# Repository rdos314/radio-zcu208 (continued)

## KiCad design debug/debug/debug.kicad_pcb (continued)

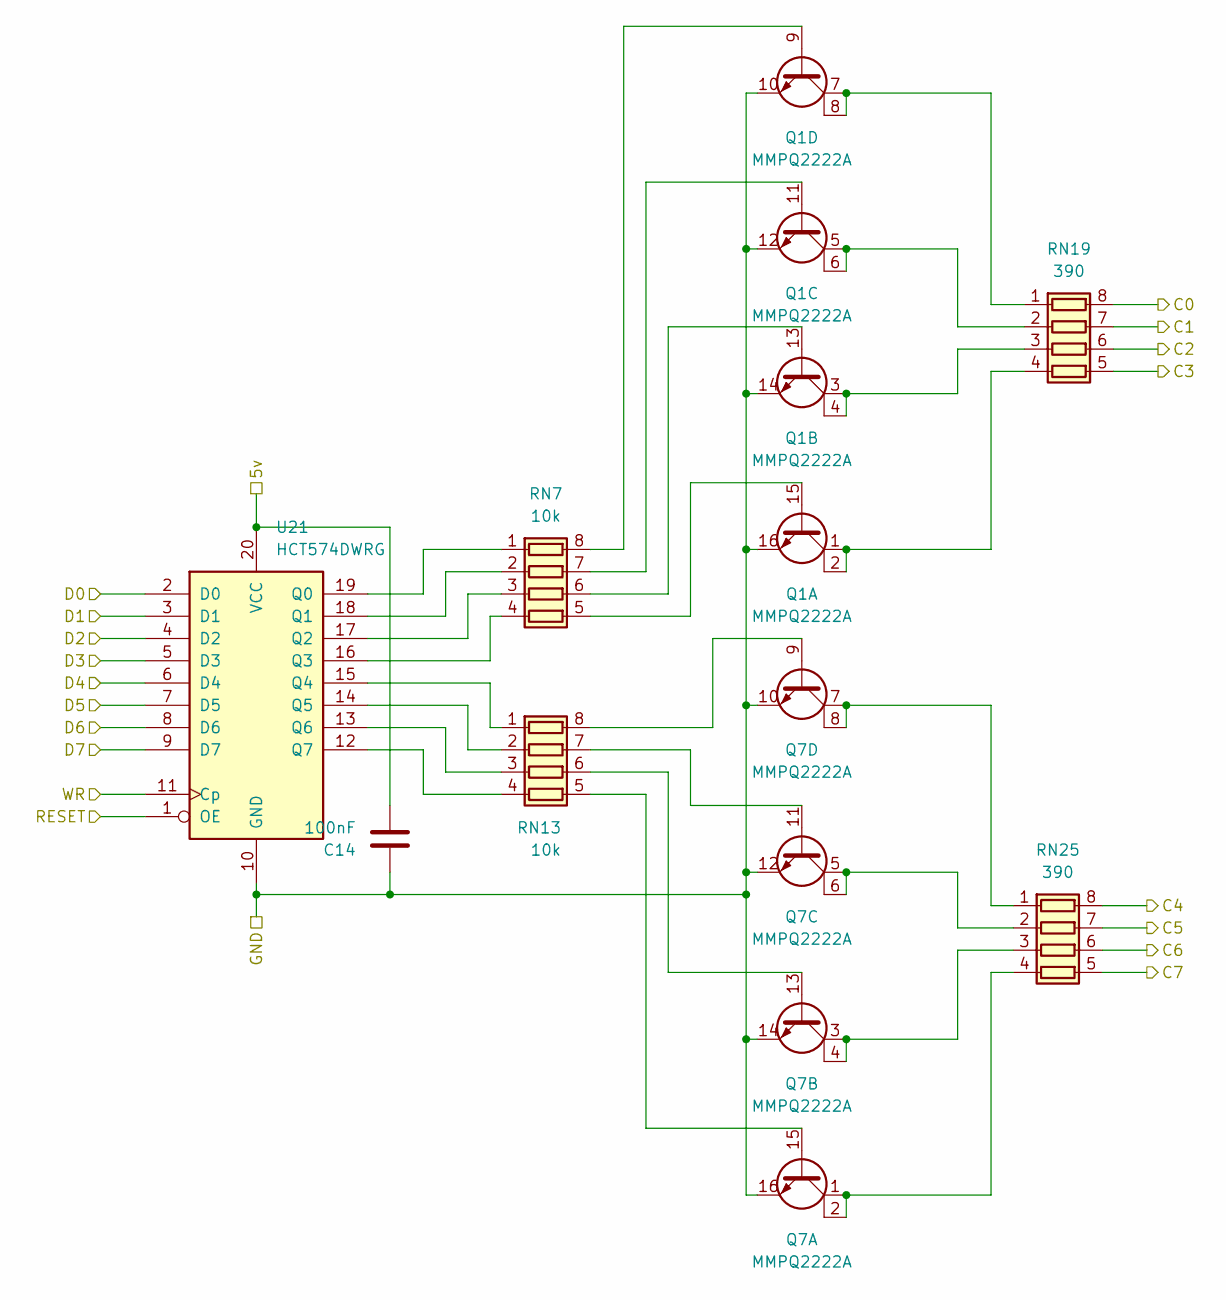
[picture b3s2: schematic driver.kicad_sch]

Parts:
C14: 100nF; C_0805_2012Metric_Pad1.18x1.45mm_HandSolder
Q1, Q7: MMPQ2222A; SO-16_3.9x9.9mm_P1.27mm
RN7, RN13: 10k; R_Array_Convex_4x0603
RN19, RN25: 390; R_Array_Convex_4x0603
U21: HCT574DWRG; SOIC-20W_7.5x12.8mm_P1.27mm

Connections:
5v: C14.2, U21.20 (VCC); also elsewhere on the board
/Band_Low/driver-LSB/C0: RN19.8 (R1.2); also elsewhere on the board
/Band_Low/driver-LSB/C1: RN19.7 (R2.2); also elsewhere on the board
/Band_Low/driver-LSB/C2: RN19.6 (R3.2); also elsewhere on the board
/Band_Low/driver-LSB/C3: RN19.5 (R4.2); also elsewhere on the board
/Band_Low/driver-LSB/C4: RN25.8 (R1.2); also elsewhere on the board
/Band_Low/driver-LSB/C5: RN25.7 (R2.2); also elsewhere on the board
/Band_Low/driver-LSB/C6: RN25.6 (R3.2); also elsewhere on the board
/Band_Low/driver-LSB/C7: RN25.5 (R4.2); also elsewhere on the board
D0: U21.2 (D0); also elsewhere on the board
D1: U21.3 (D1); also elsewhere on the board
D2: U21.4 (D2); also elsewhere on the board
D3: U21.5 (D3); also elsewhere on the board
D4: U21.6 (D4); also elsewhere on the board
D5: U21.7 (D5); also elsewhere on the board
D6: U21.8 (D6); also elsewhere on the board
D7: U21.9 (D7); also elsewhere on the board
GND: C14.1, Q1.10 (E), Q1.12 (E), Q1.14 (E), Q1.16 (E), Q7.10 (E), Q7.12 (E), Q7.14 (E), Q7.16 (E), U21.10 (GND); also elsewhere on the board
LED_LSB_LOW_WR: U21.11 (Cp); also elsewhere on the board
LED_RESET: U21.1 (OE); also elsewhere on the board
unnamed: Q1.15 (B), RN7.5 (R4.2)
unnamed: Q1.13 (B), RN7.6 (R3.2)
unnamed: Q1.11 (B), RN7.7 (R2.2)
unnamed: Q1.9 (B), RN7.8 (R1.2)
unnamed: Q7.15 (B), RN13.5 (R4.2)
unnamed: Q7.13 (B), RN13.6 (R3.2)
unnamed: Q7.11 (B), RN13.7 (R2.2)
unnamed: Q7.9 (B), RN13.8 (R1.2)
unnamed: RN7.1 (R1.1), U21.19 (Q0)
unnamed: RN7.2 (R2.1), U21.18 (Q1)
unnamed: RN7.3 (R3.1), U21.17 (Q2)
unnamed: RN7.4 (R4.1), U21.16 (Q3)
unnamed: RN13.1 (R1.1), U21.15 (Q4)
unnamed: RN13.2 (R2.1), U21.14 (Q5)
unnamed: RN13.3 (R3.1), U21.13 (Q6)
unnamed: RN13.4 (R4.1), U21.12 (Q7)
unnamed: Q1.7 (C), Q1.8 (C), RN19.1 (R1.1)
unnamed: Q1.5 (C), Q1.6 (C), RN19.2 (R2.1)
unnamed: Q1.3 (C), Q1.4 (C), RN19.3 (R3.1)
unnamed: Q1.1 (C), Q1.2 (C), RN19.4 (R4.1)
unnamed: Q7.7 (C), Q7.8 (C), RN25.1 (R1.1)
unnamed: Q7.5 (C), Q7.6 (C), RN25.2 (R2.1)
unnamed: Q7.3 (C), Q7.4 (C), RN25.3 (R3.1)
unnamed: Q7.1 (C), Q7.2 (C), RN25.4 (R4.1)

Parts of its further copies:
C16, C17, C18, C19, C20, C21: 100nF; C_0805_2012Metric_Pad1.18x1.45mm_HandSolder
Q2, Q3, Q4, Q5, Q6, Q8, Q9, Q10, Q11, Q12, Q13, Q14: MMPQ2222A; SO-16_3.9x9.9mm_P1.27mm
RN8, RN9, RN10, RN11, RN12, RN14, RN15, RN16, RN17, RN18, RN31, RN32: 10k; R_Array_Convex_4x0603
RN20, RN21, RN22, RN23, RN24, RN26, RN27, RN28, RN29, RN30, RN33, RN34: 390; R_Array_Convex_4x0603
U22, U23, U24, U25, U26, U27: HCT574DWRG; SOIC-20W_7.5x12.8mm_P1.27mm

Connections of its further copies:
5v: C16.2, C17.2, C18.2, C19.2, C20.2, C21.2, U22.20 (VCC), U23.20 (VCC), U24.20 (VCC), U25.20 (VCC), U26.20 (VCC), U27.20 (VCC); also elsewhere on the board
/Band_High/driver-LSB/C0: RN20.8 (R1.2); also elsewhere on the board
/Band_High/driver-LSB/C1: RN20.7 (R2.2); also elsewhere on the board
/Band_High/driver-LSB/C2: RN20.6 (R3.2); also elsewhere on the board
/Band_High/driver-LSB/C3: RN20.5 (R4.2); also elsewhere on the board
/Band_High/driver-LSB/C4: RN26.8 (R1.2); also elsewhere on the board
/Band_High/driver-LSB/C5: RN26.7 (R2.2); also elsewhere on the board
/Band_High/driver-LSB/C6: RN26.6 (R3.2); also elsewhere on the board
/Band_High/driver-LSB/C7: RN26.5 (R4.2); also elsewhere on the board
/Band_High/driver-MSB/C0: RN22.8 (R1.2); also elsewhere on the board
/Band_High/driver-MSB/C1: RN22.7 (R2.2); also elsewhere on the board
/Band_High/driver-MSB/C2: RN22.6 (R3.2); also elsewhere on the board
/Band_High/driver-MSB/C3: RN22.5 (R4.2); also elsewhere on the board
/Band_High/driver-MSB/C4: RN28.8 (R1.2); also elsewhere on the board
/Band_High/driver-MSB/C5: RN28.7 (R2.2); also elsewhere on the board
/Band_High/driver-MSB/C6: RN28.6 (R3.2); also elsewhere on the board
/Band_High/driver-MSB/C7: RN28.5 (R4.2); also elsewhere on the board
/Band_High/driver-dir/C0: RN24.8 (R1.2); also elsewhere on the board
/Band_High/driver-dir/C1: RN24.7 (R2.2); also elsewhere on the board
/Band_High/driver-dir/C2: RN24.6 (R3.2); also elsewhere on the board
/Band_High/driver-dir/C3: RN24.5 (R4.2); also elsewhere on the board
/Band_High/driver-dir/C4: RN30.8 (R1.2); also elsewhere on the board
/Band_High/driver-dir/C5: RN30.7 (R2.2); also elsewhere on the board
/Band_High/driver-dir/C6: RN30.6 (R3.2); also elsewhere on the board
/Band_High/driver-dir/C7: RN30.5 (R4.2); also elsewhere on the board
/Band_Low/driver-MSB/C0: RN21.8 (R1.2); also elsewhere on the board
/Band_Low/driver-MSB/C1: RN21.7 (R2.2); also elsewhere on the board
/Band_Low/driver-MSB/C2: RN21.6 (R3.2); also elsewhere on the board
/Band_Low/driver-MSB/C3: RN21.5 (R4.2); also elsewhere on the board
/Band_Low/driver-MSB/C4: RN27.8 (R1.2); also elsewhere on the board
/Band_Low/driver-MSB/C5: RN27.7 (R2.2); also elsewhere on the board
/Band_Low/driver-MSB/C6: RN27.6 (R3.2); also elsewhere on the board
/Band_Low/driver-MSB/C7: RN27.5 (R4.2); also elsewhere on the board
/Band_Low/driver-dir/C0: RN23.8 (R1.2); also elsewhere on the board
/Band_Low/driver-dir/C1: RN23.7 (R2.2); also elsewhere on the board
/Band_Low/driver-dir/C2: RN23.6 (R3.2); also elsewhere on the board
/Band_Low/driver-dir/C3: RN23.5 (R4.2); also elsewhere on the board
/Band_Low/driver-dir/C4: RN29.8 (R1.2); also elsewhere on the board
/Band_Low/driver-dir/C5: RN29.7 (R2.2); also elsewhere on the board
/Band_Low/driver-dir/C6: RN29.6 (R3.2); also elsewhere on the board
/Band_Low/driver-dir/C7: RN29.5 (R4.2); also elsewhere on the board
/driver-status/C0: RN34.8 (R1.2); also elsewhere on the board
/driver-status/C1: RN34.7 (R2.2); also elsewhere on the board
/driver-status/C2: RN34.6 (R3.2); also elsewhere on the board
/driver-status/C3: RN34.5 (R4.2); also elsewhere on the board
/driver-status/C4: RN33.8 (R1.2); also elsewhere on the board
/driver-status/C5: RN33.7 (R2.2); also elsewhere on the board
D0: U22.2 (D0), U23.2 (D0), U24.2 (D0), U25.2 (D0), U26.2 (D0), U27.2 (D0); also elsewhere on the board
D1: U22.3 (D1), U23.3 (D1), U24.3 (D1), U25.3 (D1), U26.3 (D1), U27.3 (D1); also elsewhere on the board
D2: U22.4 (D2), U23.4 (D2), U24.4 (D2), U25.4 (D2), U26.4 (D2), U27.4 (D2); also elsewhere on the board
D3: U22.5 (D3), U23.5 (D3), U24.5 (D3), U25.5 (D3), U26.5 (D3), U27.5 (D3); also elsewhere on the board
D4: U22.6 (D4), U23.6 (D4), U24.6 (D4), U25.6 (D4), U26.6 (D4), U27.6 (D4); also elsewhere on the board
D5: U22.7 (D5), U23.7 (D5), U24.7 (D5), U25.7 (D5), U26.7 (D5), U27.7 (D5); also elsewhere on the board
D6: U22.8 (D6), U23.8 (D6), U24.8 (D6), U25.8 (D6), U26.8 (D6), U27.8 (D6); also elsewhere on the board
D7: U22.9 (D7), U23.9 (D7), U24.9 (D7), U25.9 (D7), U26.9 (D7), U27.9 (D7); also elsewhere on the board
DIR_HIGH_ERR: RN33.5 (R4.2); also elsewhere on the board
DIR_HIGH_WR: U26.11 (Cp); also elsewhere on the board
DIR_LOW_ERR: RN33.6 (R3.2); also elsewhere on the board
DIR_LOW_WR: U25.11 (Cp); also elsewhere on the board
GND: C16.1, C17.1, C18.1, C19.1, C20.1, C21.1, Q2.10 (E), Q2.12 (E), Q2.14 (E), Q2.16 (E), Q3.10 (E), Q3.12 (E), Q3.14 (E), Q3.16 (E), Q4.10 (E), Q4.12 (E), Q4.14 (E), Q4.16 (E), Q5.10 (E), Q5.12 (E), Q5.14 (E), Q5.16 (E), Q6.10 (E), Q6.12 (E), Q6.14 (E), Q6.16 (E), Q8.10 (E), Q8.12 (E), Q8.14 (E), Q8.16 (E), Q9.10 (E), Q9.12 (E), Q9.14 (E), Q9.16 (E), Q10.10 (E), Q10.12 (E), Q10.14 (E), Q10.16 (E), Q11.10 (E), Q11.12 (E), Q11.14 (E), Q11.16 (E), Q12.10 (E), Q12.12 (E), Q12.14 (E), Q12.16 (E), Q13.10 (E), Q13.12 (E), Q13.14 (E), Q13.16 (E), Q14.10 (E), Q14.12 (E), Q14.14 (E), Q14.16 (E), U22.10 (GND), U23.10 (GND), U24.10 (GND), U25.10 (GND), U26.10 (GND), U27.10 (GND); also elsewhere on the board
LED_LSB_HIGH_WR: U22.11 (Cp); also elsewhere on the board
LED_MSB_HIGH_WR: U24.11 (Cp); also elsewhere on the board
LED_MSB_LOW_WR: U23.11 (Cp); also elsewhere on the board
LED_RESET: U22.1 (OE), U23.1 (OE), U24.1 (OE), U25.1 (OE), U26.1 (OE), U27.1 (OE); also elsewhere on the board
unnamed: Q2.15 (B), RN8.5 (R4.2)
unnamed: Q2.13 (B), RN8.6 (R3.2)
unnamed: Q2.11 (B), RN8.7 (R2.2)
unnamed: Q2.9 (B), RN8.8 (R1.2)
unnamed: Q3.15 (B), RN9.5 (R4.2)
unnamed: Q3.13 (B), RN9.6 (R3.2)
unnamed: Q3.11 (B), RN9.7 (R2.2)
unnamed: Q3.9 (B), RN9.8 (R1.2)
unnamed: Q4.15 (B), RN10.5 (R4.2)
unnamed: Q4.13 (B), RN10.6 (R3.2)
unnamed: Q4.11 (B), RN10.7 (R2.2)
unnamed: Q4.9 (B), RN10.8 (R1.2)
unnamed: Q5.15 (B), RN11.5 (R4.2)
unnamed: Q5.13 (B), RN11.6 (R3.2)
unnamed: Q5.11 (B), RN11.7 (R2.2)
unnamed: Q5.9 (B), RN11.8 (R1.2)
unnamed: Q6.15 (B), RN12.5 (R4.2)
unnamed: Q6.13 (B), RN12.6 (R3.2)
unnamed: Q6.11 (B), RN12.7 (R2.2)
unnamed: Q6.9 (B), RN12.8 (R1.2)
unnamed: Q8.15 (B), RN14.5 (R4.2)
unnamed: Q8.13 (B), RN14.6 (R3.2)
unnamed: Q8.11 (B), RN14.7 (R2.2)
unnamed: Q8.9 (B), RN14.8 (R1.2)
unnamed: Q9.15 (B), RN15.5 (R4.2)
unnamed: Q9.13 (B), RN15.6 (R3.2)
unnamed: Q9.11 (B), RN15.7 (R2.2)
unnamed: Q9.9 (B), RN15.8 (R1.2)
unnamed: Q10.15 (B), RN16.5 (R4.2)
unnamed: Q10.13 (B), RN16.6 (R3.2)
unnamed: Q10.11 (B), RN16.7 (R2.2)
unnamed: Q10.9 (B), RN16.8 (R1.2)
unnamed: Q11.15 (B), RN17.5 (R4.2)
unnamed: Q11.13 (B), RN17.6 (R3.2)
unnamed: Q11.11 (B), RN17.7 (R2.2)
unnamed: Q11.9 (B), RN17.8 (R1.2)
unnamed: Q12.15 (B), RN18.5 (R4.2)
unnamed: Q12.13 (B), RN18.6 (R3.2)
unnamed: Q12.11 (B), RN18.7 (R2.2)
unnamed: Q12.9 (B), RN18.8 (R1.2)
unnamed: Q13.15 (B), RN31.5 (R4.2)
unnamed: Q13.13 (B), RN31.6 (R3.2)
unnamed: Q13.11 (B), RN31.7 (R2.2)
unnamed: Q13.9 (B), RN31.8 (R1.2)
unnamed: Q14.15 (B), RN32.5 (R4.2)
unnamed: Q14.13 (B), RN32.6 (R3.2)
unnamed: Q14.11 (B), RN32.7 (R2.2)
unnamed: Q14.9 (B), RN32.8 (R1.2)
unnamed: RN8.1 (R1.1), U22.19 (Q0)
unnamed: RN8.2 (R2.1), U22.18 (Q1)
unnamed: RN8.3 (R3.1), U22.17 (Q2)
unnamed: RN8.4 (R4.1), U22.16 (Q3)
unnamed: RN9.1 (R1.1), U23.19 (Q0)
unnamed: RN9.2 (R2.1), U23.18 (Q1)
unnamed: RN9.3 (R3.1), U23.17 (Q2)
unnamed: RN9.4 (R4.1), U23.16 (Q3)
unnamed: RN10.1 (R1.1), U24.19 (Q0)
unnamed: RN10.2 (R2.1), U24.18 (Q1)
unnamed: RN10.3 (R3.1), U24.17 (Q2)
unnamed: RN10.4 (R4.1), U24.16 (Q3)
unnamed: RN11.1 (R1.1), U25.19 (Q0)
unnamed: RN11.2 (R2.1), U25.18 (Q1)
unnamed: RN11.3 (R3.1), U25.17 (Q2)
unnamed: RN11.4 (R4.1), U25.16 (Q3)
unnamed: RN12.1 (R1.1), U26.19 (Q0)
unnamed: RN12.2 (R2.1), U26.18 (Q1)
unnamed: RN12.3 (R3.1), U26.17 (Q2)
unnamed: RN12.4 (R4.1), U26.16 (Q3)
unnamed: RN14.1 (R1.1), U22.15 (Q4)
unnamed: RN14.2 (R2.1), U22.14 (Q5)
unnamed: RN14.3 (R3.1), U22.13 (Q6)
unnamed: RN14.4 (R4.1), U22.12 (Q7)
unnamed: RN15.1 (R1.1), U23.15 (Q4)
unnamed: RN15.2 (R2.1), U23.14 (Q5)
unnamed: RN15.3 (R3.1), U23.13 (Q6)
unnamed: RN15.4 (R4.1), U23.12 (Q7)
unnamed: RN16.1 (R1.1), U24.15 (Q4)
unnamed: RN16.2 (R2.1), U24.14 (Q5)
unnamed: RN16.3 (R3.1), U24.13 (Q6)
unnamed: RN16.4 (R4.1), U24.12 (Q7)
unnamed: RN17.1 (R1.1), U25.15 (Q4)
unnamed: RN17.2 (R2.1), U25.14 (Q5)
unnamed: RN17.3 (R3.1), U25.13 (Q6)
unnamed: RN17.4 (R4.1), U25.12 (Q7)
unnamed: RN18.1 (R1.1), U26.15 (Q4)
unnamed: RN18.2 (R2.1), U26.14 (Q5)
unnamed: RN18.3 (R3.1), U26.13 (Q6)
unnamed: RN18.4 (R4.1), U26.12 (Q7)
unnamed: Q2.7 (C), Q2.8 (C), RN20.1 (R1.1)
unnamed: Q2.5 (C), Q2.6 (C), RN20.2 (R2.1)
unnamed: Q2.3 (C), Q2.4 (C), RN20.3 (R3.1)
unnamed: Q2.1 (C), Q2.2 (C), RN20.4 (R4.1)
unnamed: Q3.7 (C), Q3.8 (C), RN21.1 (R1.1)
unnamed: Q3.5 (C), Q3.6 (C), RN21.2 (R2.1)
unnamed: Q3.3 (C), Q3.4 (C), RN21.3 (R3.1)
unnamed: Q3.1 (C), Q3.2 (C), RN21.4 (R4.1)
unnamed: Q4.7 (C), Q4.8 (C), RN22.1 (R1.1)
unnamed: Q4.5 (C), Q4.6 (C), RN22.2 (R2.1)
unnamed: Q4.3 (C), Q4.4 (C), RN22.3 (R3.1)
unnamed: Q4.1 (C), Q4.2 (C), RN22.4 (R4.1)
unnamed: Q5.7 (C), Q5.8 (C), RN23.1 (R1.1)
unnamed: Q5.5 (C), Q5.6 (C), RN23.2 (R2.1)
unnamed: Q5.3 (C), Q5.4 (C), RN23.3 (R3.1)
unnamed: Q5.1 (C), Q5.2 (C), RN23.4 (R4.1)
unnamed: Q6.7 (C), Q6.8 (C), RN24.1 (R1.1)
unnamed: Q6.5 (C), Q6.6 (C), RN24.2 (R2.1)
unnamed: Q6.3 (C), Q6.4 (C), RN24.3 (R3.1)
unnamed: Q6.1 (C), Q6.2 (C), RN24.4 (R4.1)
unnamed: Q8.7 (C), Q8.8 (C), RN26.1 (R1.1)
unnamed: Q8.5 (C), Q8.6 (C), RN26.2 (R2.1)
unnamed: Q8.3 (C), Q8.4 (C), RN26.3 (R3.1)
unnamed: Q8.1 (C), Q8.2 (C), RN26.4 (R4.1)
unnamed: Q9.7 (C), Q9.8 (C), RN27.1 (R1.1)
unnamed: Q9.5 (C), Q9.6 (C), RN27.2 (R2.1)
unnamed: Q9.3 (C), Q9.4 (C), RN27.3 (R3.1)
unnamed: Q9.1 (C), Q9.2 (C), RN27.4 (R4.1)
unnamed: Q10.7 (C), Q10.8 (C), RN28.1 (R1.1)
unnamed: Q10.5 (C), Q10.6 (C), RN28.2 (R2.1)
unnamed: Q10.3 (C), Q10.4 (C), RN28.3 (R3.1)
unnamed: Q10.1 (C), Q10.2 (C), RN28.4 (R4.1)
unnamed: Q11.7 (C), Q11.8 (C), RN29.1 (R1.1)
unnamed: Q11.5 (C), Q11.6 (C), RN29.2 (R2.1)
unnamed: Q11.3 (C), Q11.4 (C), RN29.3 (R3.1)
unnamed: Q11.1 (C), Q11.2 (C), RN29.4 (R4.1)
unnamed: Q12.7 (C), Q12.8 (C), RN30.1 (R1.1)
unnamed: Q12.5 (C), Q12.6 (C), RN30.2 (R2.1)
unnamed: Q12.3 (C), Q12.4 (C), RN30.3 (R3.1)
unnamed: Q12.1 (C), Q12.2 (C), RN30.4 (R4.1)
unnamed: RN31.1 (R1.1), U27.19 (Q0)
unnamed: RN31.2 (R2.1), U27.18 (Q1)
unnamed: RN31.3 (R3.1), U27.17 (Q2)
unnamed: RN31.4 (R4.1), U27.16 (Q3)
unnamed: RN32.1 (R1.1), U27.15 (Q4)
unnamed: RN32.2 (R2.1), U27.14 (Q5)
unnamed: RN32.3 (R3.1), U27.13 (Q6)
unnamed: RN32.4 (R4.1), U27.12 (Q7)
unnamed: Q14.7 (C), Q14.8 (C), RN33.1 (R1.1)
unnamed: Q14.5 (C), Q14.6 (C), RN33.2 (R2.1)
unnamed: Q14.3 (C), Q14.4 (C), RN33.3 (R3.1)
unnamed: Q14.1 (C), Q14.2 (C), RN33.4 (R4.1)
unnamed: Q13.7 (C), Q13.8 (C), RN34.1 (R1.1)
unnamed: Q13.5 (C), Q13.6 (C), RN34.2 (R2.1)
unnamed: Q13.3 (C), Q13.4 (C), RN34.3 (R3.1)
unnamed: Q13.1 (C), Q13.2 (C), RN34.4 (R4.1)
STAT_WR: U27.11 (Cp); also elsewhere on the board

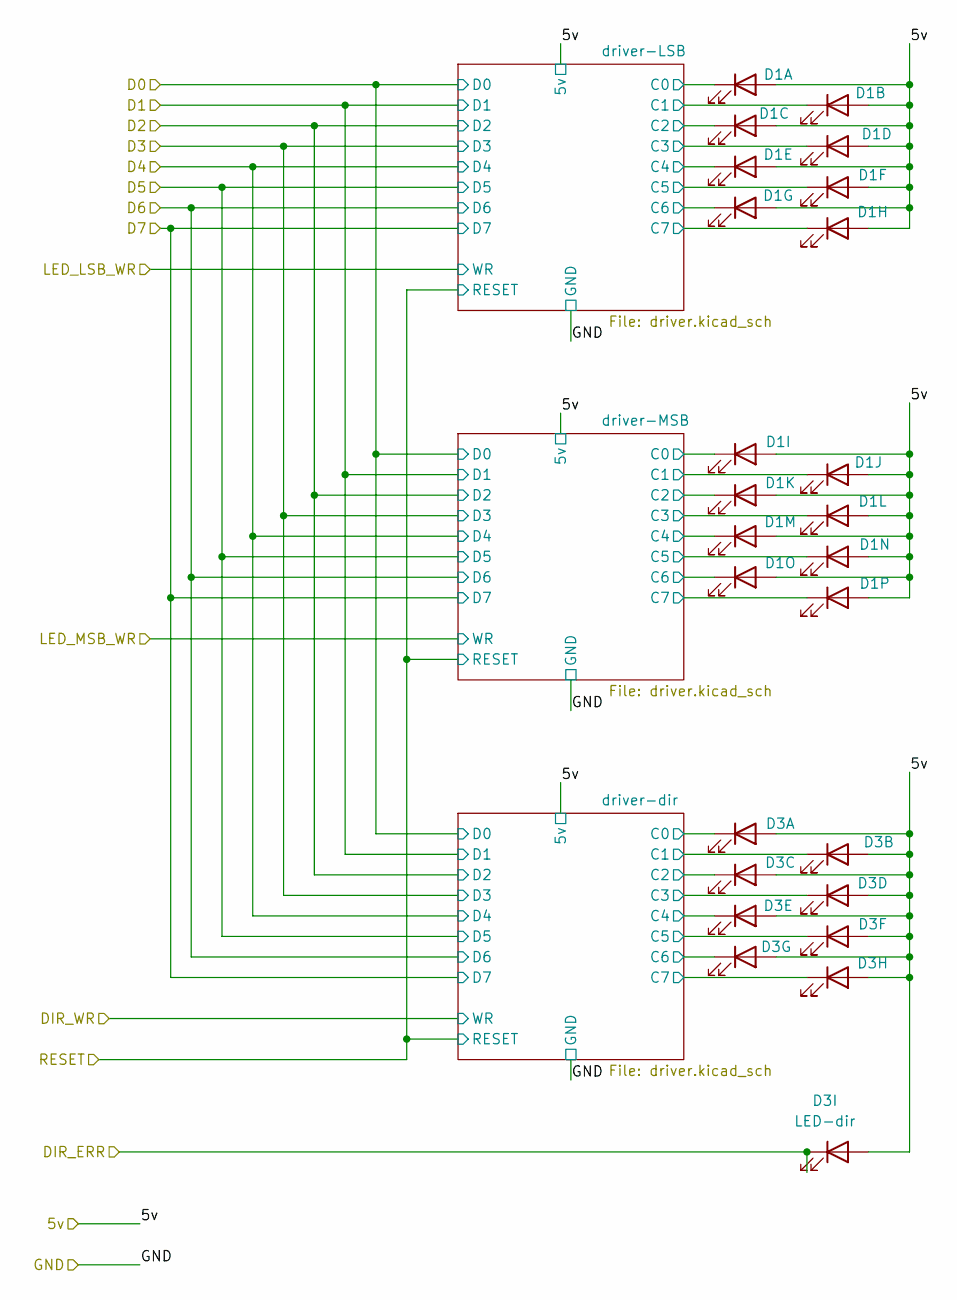
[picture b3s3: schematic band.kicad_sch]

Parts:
D1: LED-16x
D3: LED-dir

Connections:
5v: D1.2 (A), D1.4 (A), D1.6 (A), D1.8 (A), D1.10 (A), D1.12 (A), D1.14 (A), D1.16 (A), D1.18 (A), D1.20 (A), D1.22 (A), D1.24 (A), D1.26 (A), D1.28 (A), D1.30 (A), D1.32 (A), D3.2 (A), D3.4 (A), D3.6 (A), D3.8 (A), D3.10 (A), D3.12 (A), D3.14 (A), D3.16 (A), D3.18 (A); also elsewhere on the board
/Band_Low/driver-LSB/C0: D1.1 (K); also elsewhere on the board
/Band_Low/driver-LSB/C1: D1.3 (K); also elsewhere on the board
/Band_Low/driver-LSB/C2: D1.5 (K); also elsewhere on the board
/Band_Low/driver-LSB/C3: D1.7 (K); also elsewhere on the board
/Band_Low/driver-LSB/C4: D1.9 (K); also elsewhere on the board
/Band_Low/driver-LSB/C5: D1.11 (K); also elsewhere on the board
/Band_Low/driver-LSB/C6: D1.13 (K); also elsewhere on the board
/Band_Low/driver-LSB/C7: D1.15 (K); also elsewhere on the board
/Band_Low/driver-MSB/C0: D1.17 (K); also elsewhere on the board
/Band_Low/driver-MSB/C1: D1.19 (K); also elsewhere on the board
/Band_Low/driver-MSB/C2: D1.21 (K); also elsewhere on the board
/Band_Low/driver-MSB/C3: D1.23 (K); also elsewhere on the board
/Band_Low/driver-MSB/C4: D1.25 (K); also elsewhere on the board
/Band_Low/driver-MSB/C5: D1.27 (K); also elsewhere on the board
/Band_Low/driver-MSB/C6: D1.29 (K); also elsewhere on the board
/Band_Low/driver-MSB/C7: D1.31 (K); also elsewhere on the board
/Band_Low/driver-dir/C0: D3.1 (K); also elsewhere on the board
/Band_Low/driver-dir/C1: D3.3 (K); also elsewhere on the board
/Band_Low/driver-dir/C2: D3.5 (K); also elsewhere on the board
/Band_Low/driver-dir/C3: D3.7 (K); also elsewhere on the board
/Band_Low/driver-dir/C4: D3.9 (K); also elsewhere on the board
/Band_Low/driver-dir/C5: D3.11 (K); also elsewhere on the board
/Band_Low/driver-dir/C6: D3.13 (K); also elsewhere on the board
/Band_Low/driver-dir/C7: D3.15 (K); also elsewhere on the board
DIR_LOW_ERR: D3.17 (K); also elsewhere on the board

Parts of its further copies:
D2: LED-16x
D4: LED-dir

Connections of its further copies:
5v: D2.2 (A), D2.4 (A), D2.6 (A), D2.8 (A), D2.10 (A), D2.12 (A), D2.14 (A), D2.16 (A), D2.18 (A), D2.20 (A), D2.22 (A), D2.24 (A), D2.26 (A), D2.28 (A), D2.30 (A), D2.32 (A), D4.2 (A), D4.4 (A), D4.6 (A), D4.8 (A), D4.10 (A), D4.12 (A), D4.14 (A), D4.16 (A), D4.18 (A); also elsewhere on the board
/Band_High/driver-LSB/C0: D2.1 (K); also elsewhere on the board
/Band_High/driver-LSB/C1: D2.3 (K); also elsewhere on the board
/Band_High/driver-LSB/C2: D2.5 (K); also elsewhere on the board
/Band_High/driver-LSB/C3: D2.7 (K); also elsewhere on the board
/Band_High/driver-LSB/C4: D2.9 (K); also elsewhere on the board
/Band_High/driver-LSB/C5: D2.11 (K); also elsewhere on the board
/Band_High/driver-LSB/C6: D2.13 (K); also elsewhere on the board
/Band_High/driver-LSB/C7: D2.15 (K); also elsewhere on the board
/Band_High/driver-MSB/C0: D2.17 (K); also elsewhere on the board
/Band_High/driver-MSB/C1: D2.19 (K); also elsewhere on the board
/Band_High/driver-MSB/C2: D2.21 (K); also elsewhere on the board
/Band_High/driver-MSB/C3: D2.23 (K); also elsewhere on the board
/Band_High/driver-MSB/C4: D2.25 (K); also elsewhere on the board
/Band_High/driver-MSB/C5: D2.27 (K); also elsewhere on the board
/Band_High/driver-MSB/C6: D2.29 (K); also elsewhere on the board
/Band_High/driver-MSB/C7: D2.31 (K); also elsewhere on the board
/Band_High/driver-dir/C0: D4.1 (K); also elsewhere on the board
/Band_High/driver-dir/C1: D4.3 (K); also elsewhere on the board
/Band_High/driver-dir/C2: D4.5 (K); also elsewhere on the board
/Band_High/driver-dir/C3: D4.7 (K); also elsewhere on the board
/Band_High/driver-dir/C4: D4.9 (K); also elsewhere on the board
/Band_High/driver-dir/C5: D4.11 (K); also elsewhere on the board
/Band_High/driver-dir/C6: D4.13 (K); also elsewhere on the board
/Band_High/driver-dir/C7: D4.15 (K); also elsewhere on the board
DIR_HIGH_ERR: D4.17 (K); also elsewhere on the board

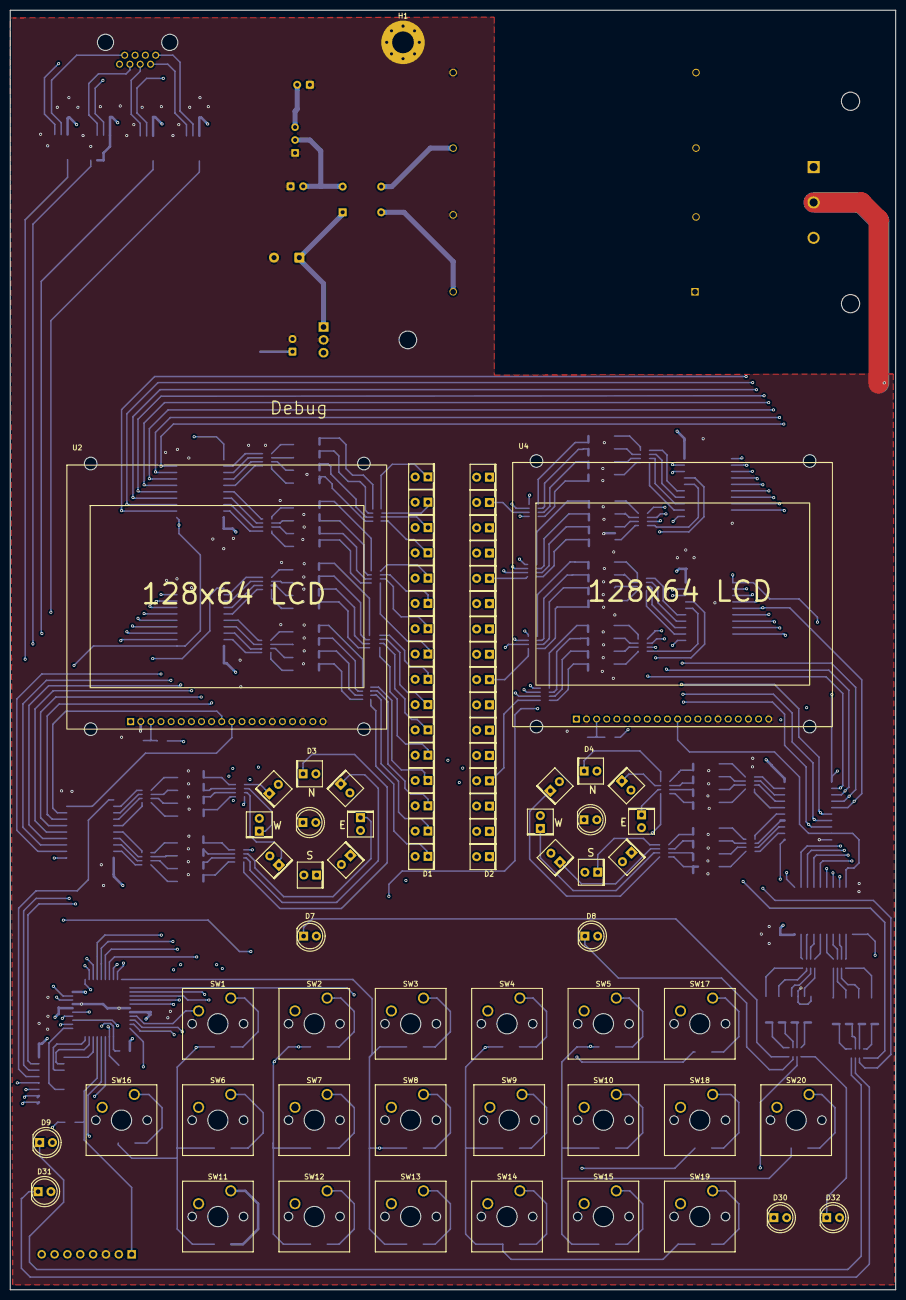
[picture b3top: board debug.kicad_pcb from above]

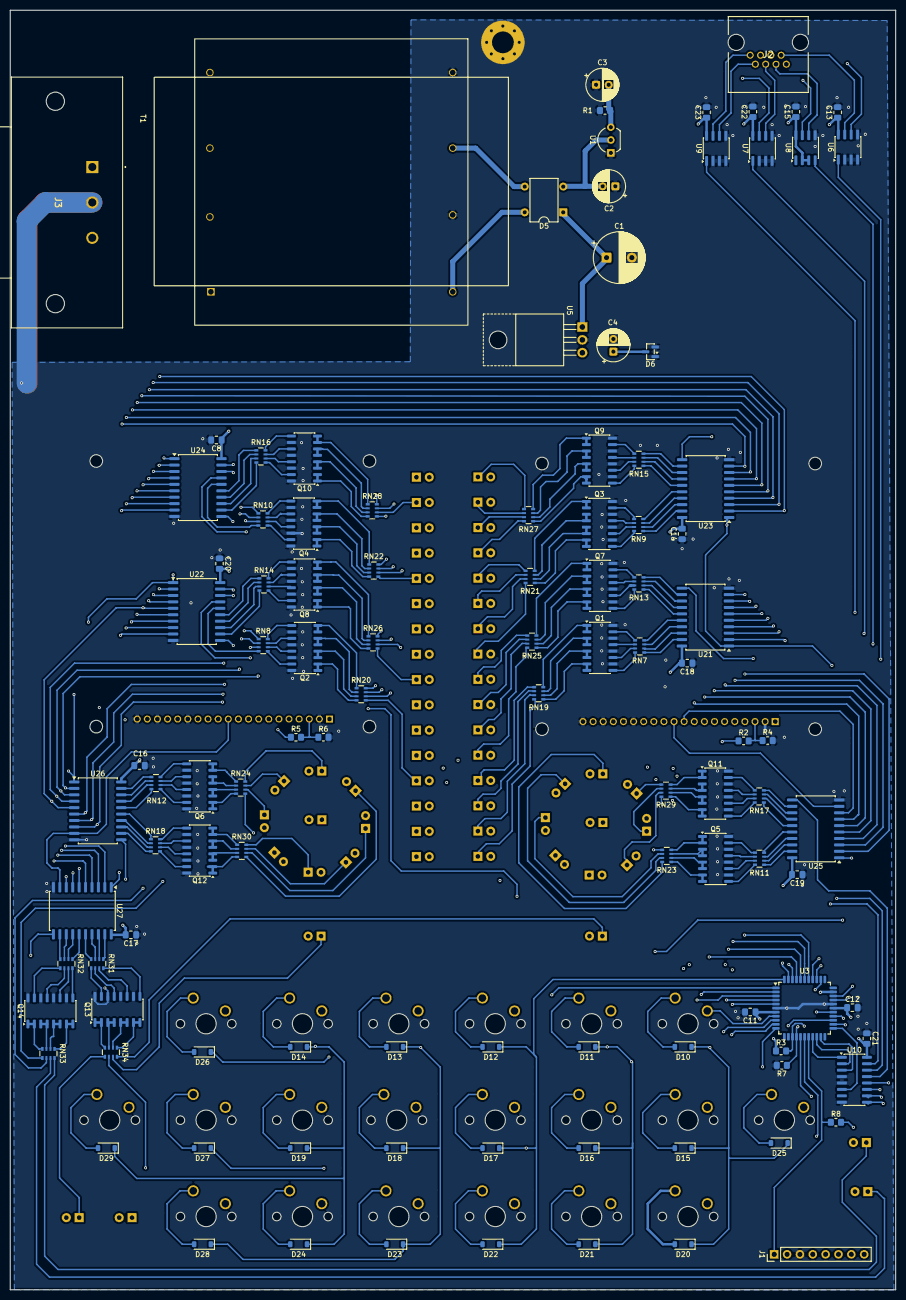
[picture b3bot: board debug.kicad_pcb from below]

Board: 4 copper layers, 175.0 x 252.9 mm, 142 parts (109 on the bottom side), 306 nets.

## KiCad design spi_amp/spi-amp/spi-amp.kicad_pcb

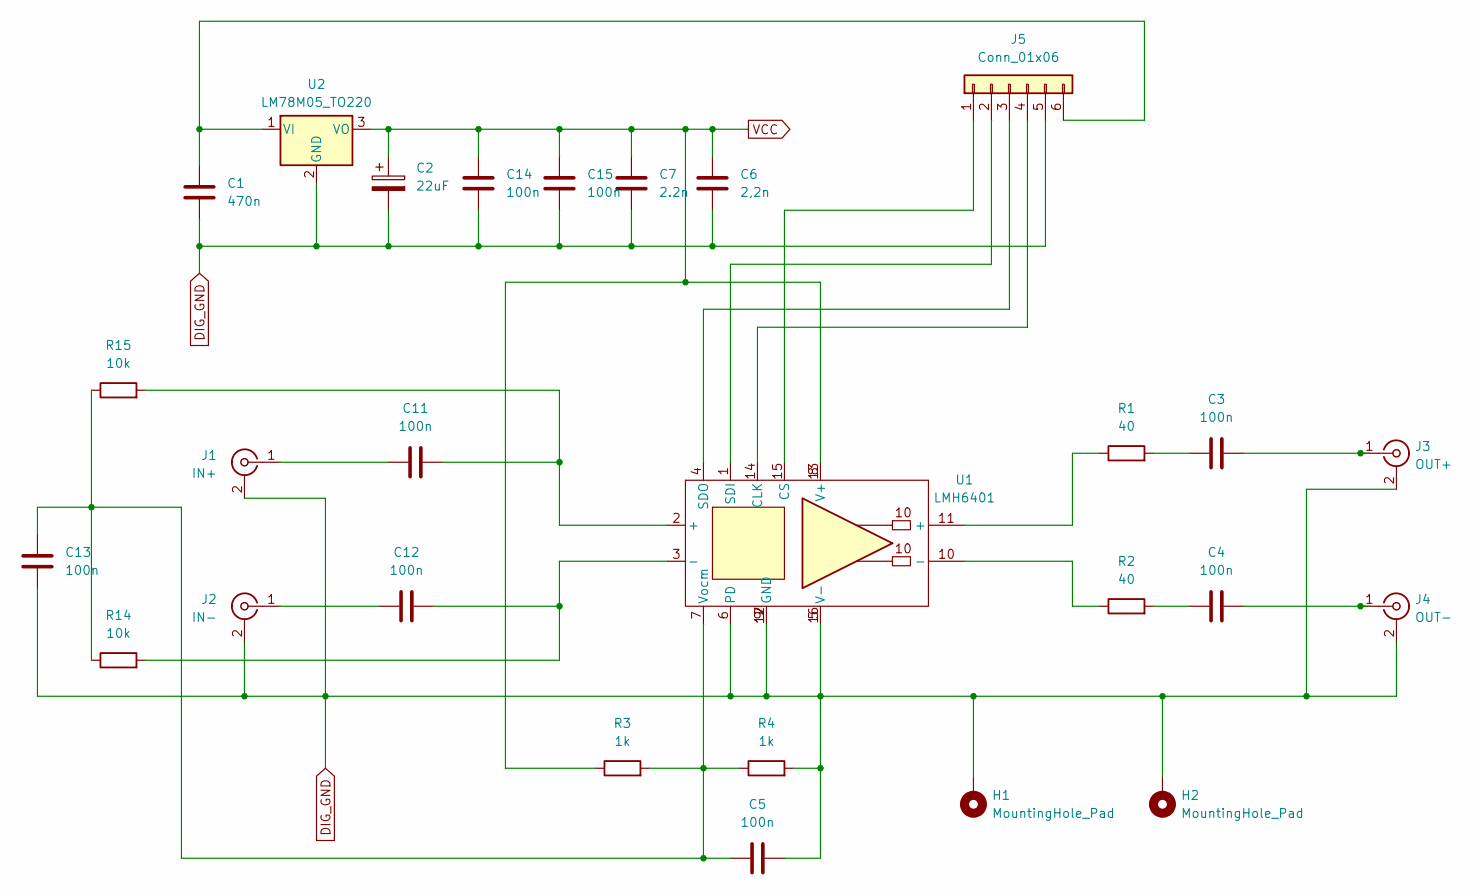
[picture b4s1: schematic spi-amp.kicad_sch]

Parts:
C1: 470n; C_Disc_D4.3mm_W1.9mm_P5.00mm
C2: 22uF; CP_Radial_D6.3mm_P2.50mm
C3, C4, C11, C12: 100n; C_0402_1005Metric_Pad0.74x0.62mm_HandSolder
C5, C13, C14, C15: 100n; C_0805_2012Metric_Pad1.18x1.45mm_HandSolder
C6: 2,2n; C_0402_1005Metric_Pad0.74x0.62mm_HandSolder
C7: 2.2n; C_0402_1005Metric_Pad0.74x0.62mm_HandSolder
H1, H2: MountingHole_Pad; MountingHole_3.2mm_M3_Pad
J1: IN+; SMA_Amphenol_132289_EdgeMount
J2: IN-; SMA_Amphenol_132289_EdgeMount
J3: OUT+; SMA_Amphenol_132289_EdgeMount
J4: OUT-; SMA_Amphenol_132289_EdgeMount
J5: Conn_01x06; PinSocket_1x06_P2.54mm_Horizontal
R1, R2: 40; R_0402_1005Metric_Pad0.72x0.64mm_HandSolder
R3, R4: 1k; R_0805_2012Metric_Pad1.20x1.40mm_HandSolder
R14, R15: 10k; R_0402_1005Metric_Pad0.72x0.64mm_HandSolder
U1: LMH6401; UQFN-16-custom
U2: LM78M05_TO220; TO-220-3_Horizontal_TabDown

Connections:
DIG_GND: C1.2, C2.2, C5.2, C6.1, C7.1, C13.1, C14.1, C15.1, H1.1 (1_1), H2.1 (1_1), J1.2 (Ext), J2.2 (Ext), J3.2 (Ext), J4.2 (Ext), J5.5, R4.2, U1.5 (V-), U1.6 (PD), U1.9 (GND), U1.12 (GND), U1.16 (V-), U1.17 (GND), U2.2 (GND)
unnamed: C3.1, R1.2
unnamed: C4.1, R2.2
unnamed: C11.2, R15.2, U1.2 (+)
unnamed: C12.2, R14.2, U1.3 (-)
unnamed: C11.1, J1.1 (In)
unnamed: C12.1, J2.1 (In)
unnamed: C3.2, J3.1 (In)
unnamed: C4.2, J4.1 (In)
unnamed: J5.1, U1.15 (CS)
unnamed: J5.2, U1.1 (SDI)
unnamed: J5.3, U1.4 (SDO)
unnamed: J5.4, U1.14 (CLK)
unnamed: C1.1, J5.6, U2.1 (VI)
unnamed: R1.1, U1.11 (+)
unnamed: R2.1, U1.10 (-)
unnamed: C5.1, C13.2, R3.2, R4.1, R14.1, R15.1, U1.7 (Vocm)
VCC: C2.1, C6.2, C7.2, C14.2, C15.2, R3.1, U1.8 (V+), U1.13 (V+), U2.3 (VO)

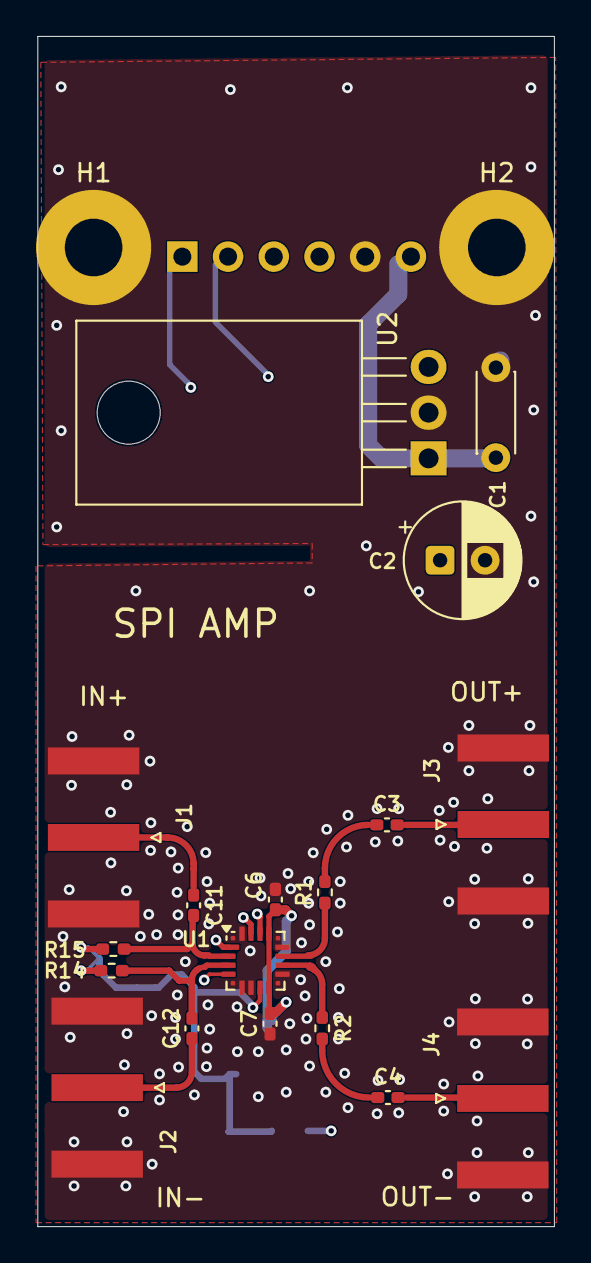
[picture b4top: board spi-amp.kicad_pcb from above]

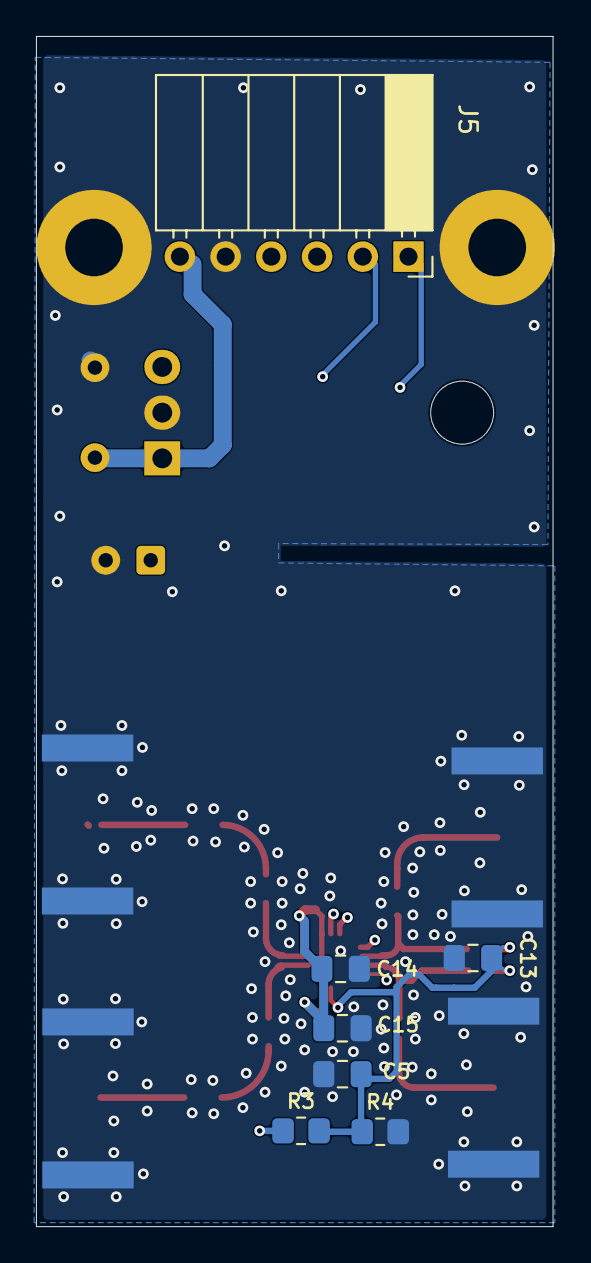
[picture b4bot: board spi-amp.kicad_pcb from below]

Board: 4 copper layers, 28.7 x 66.1 mm, 27 parts (7 on the bottom side), 18 nets.
